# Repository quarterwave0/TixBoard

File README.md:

# TixBoard - Digital Communications Education Board
### Schematic and idea derived from a [April 2022 thread from @m_ou_se on Twitter.](https://twitter.com/m_ou_se/status/1511091323612413965)

The TixBoard is a hands-on digital communications demonstration and education tool designed for everyone passionate about learning. From absolute beginners looking for a tactile introduction to how various flavors of digital communication function to experienced makers, educators, precocious cats, or bacteria looking for a unique perspective on the protocols that make our digital world tick.

## Operation

The TixBoard features a single RCA socket as its medium of communication. It utilizes inexpensive RCA cables and splitters to make arbitrary and easily reconfigurable networks of TixBoards, whether point-to-point or on a shared bus. On the board side, it features three switches that allow for the rapid and straightforward reconfiguration of any TixBoard. It is powered by two AA batteries, which should last a long time **provided that the output not be high during storage, as this will result in the LED running and draining the battery.** It is best to set the board to Hi-Z and disable the Pull-Up switch before storing your TixBoard. The "Status" LED serves as a visual indicator of both the input received by the TixBoard in input mode and the output of the TixBoard in output mode. The "Short" LED alerts the user when they have connected TixBoards in a way that will result in excessive battery drainage.

### Input(Hi-Z)/Output Switch
The Input/Output switch is used to change the behavior of the TixBoard. The TixBoard can be configured to **Input(Hi-Z)**, where the TixBoard will act as an input, simply allowing the LED to flash with the input. Input(Hi-Z) can also be used as part of three-state logic so that when it is switched to Hi-Z[^1], it will effectively not influence the communication system. When switched to output, the behavior of the TixBoard is determined by the Low/High switch.

### Low/High Switch
The **Low/High** switch determines whether the TixBoard outputs logical high or low. When set to high, the TixBoard will output a logical high. When set to low, it will bring its output to ground. If two TixBoards are connected so that the logical high output of one is sunk directly into the logical low output of another, the short LED will illuminate. Do not fear- your boards are not in peril. It is just a warning that the rate of battery drain will increase.

### Pull-Up Switch
The **Pull-Up** switch is used to make the output of the TixBoard default to logical high with the onboard 22kΩ pull-up resistor. A real-world example would be the I²C protocol, which grounds the output to produce a logical low and toggles Hi-Z to let the pull-up resistor take the output to a higher voltage to make a logical high. If the output is enabled and is low, the pull-up will sink into the low, however, the drain rate will be very low.

### Examples

For some example operations, here are some Youtube videos I made that cover two good examples: Morse code and I2C.

[Morse Code](https://youtu.be/1-J6O0SY3v4)

[I2C](https://youtu.be/L52Stvm2y-I)

### License
Hardware is covered under CERN-OHL-P v2, meaning there are some restrictions on how this can be used. Read more [here](https://choosealicense.com/licenses/cern-ohl-p-2.0/).

This file, README.md, the primary source of documentation for this device,  is covered under CC0 1.0, meaning it is free for literally anything you could dream of.

[^1]: Fancy engineering speak for high impedance, a state where the output will let minimal current through. Think of it as a floating wire, as there is no path to ground. Quite literally, the Hi-Z/Input path is a dead end.

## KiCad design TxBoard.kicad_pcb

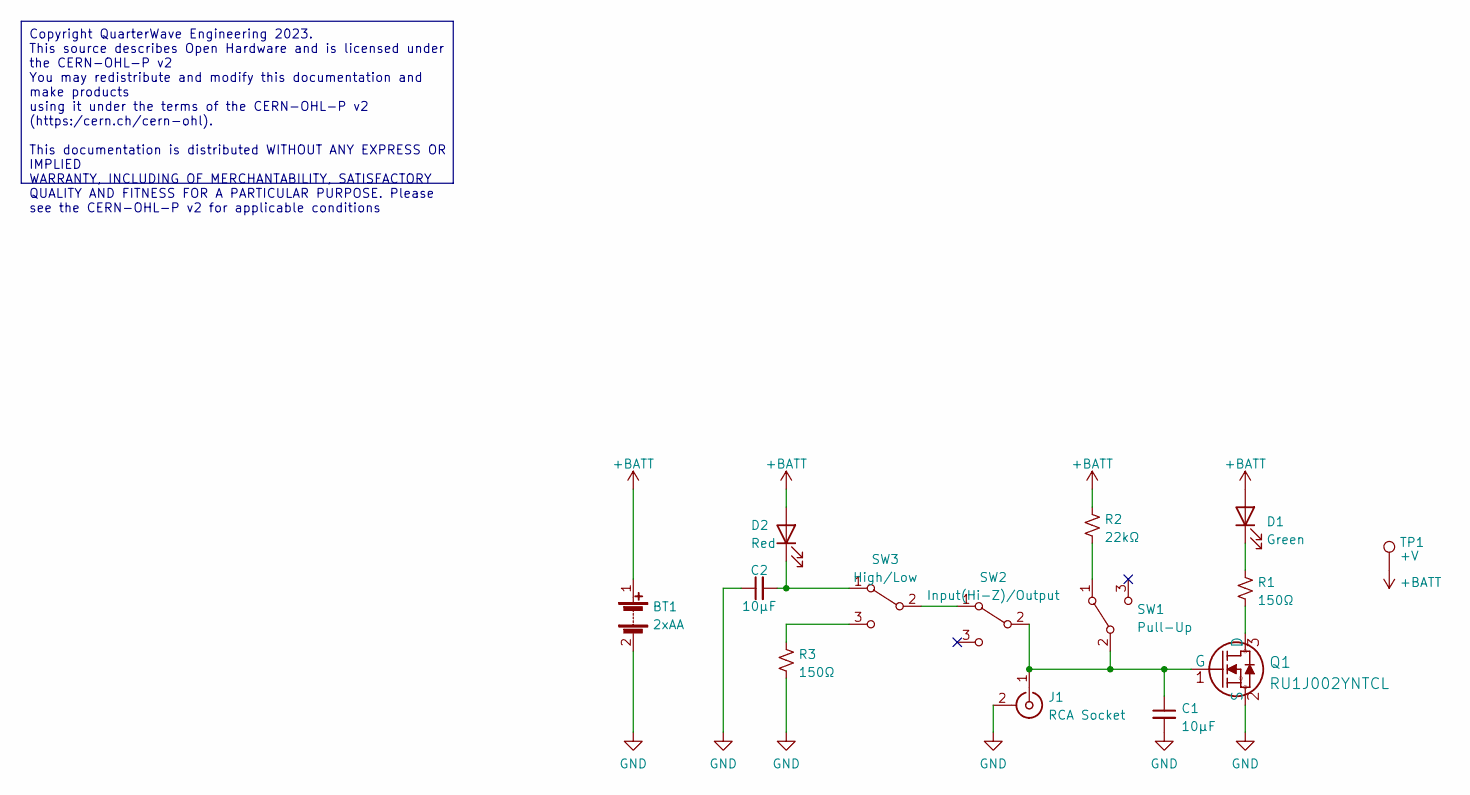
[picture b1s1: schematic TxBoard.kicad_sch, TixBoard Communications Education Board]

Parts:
BT1: 2xAA; BC2AAPC
C1, C2: 10μF; C_0805_2012Metric
D1: Green; LED_0603_1608Metric
D2: Red; LED_0603_1608Metric
J1: RCA Socket; KLPX-0848A
Q1: RU1J002YNTCL; SOT-323_SC-70
R1, R3: 150Ω; R_0603_1608Metric
R2: 22kΩ; R_0603_1608Metric
SW1: Pull-Up; JS102011SCQN
SW2: Input(Hi-Z)/Output; JS102011SCQN
SW3: High/Low; JS102011SCQN
TP1: +V; TestPoint_Pad_1.5x1.5mm

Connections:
+BATT: BT1.1 (+), D1.2 (A), D2.2 (A), R2.1, TP1.1
GND: BT1.2 (-), C1.2, C2.1, J1.2 (Ext), Q1.2 (S), R3.1
unnamed: D1.1 (K), R1.1
unnamed: C2.2, D2.1 (K), SW3.1 (A)
unnamed: C1.1, J1.1 (In), Q1.1 (G), SW1.2 (B), SW2.2 (B)
unnamed: Q1.3 (D), R1.2
unnamed: R2.2, SW1.1 (A)
unnamed: SW2.1 (A), SW3.2 (B)
unnamed: R3.2, SW3.3 (C)

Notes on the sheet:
Copyright QuarterWave Engineering 2023. This source describes Open Hardware and is licensed under the CERN-OHL-P v2 You may redistribute and modify this documentation and make products using it under the terms of the CERN-OHL-P v2 (https:/cern.ch/cern-ohl). This documentation is distributed WITHOUT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

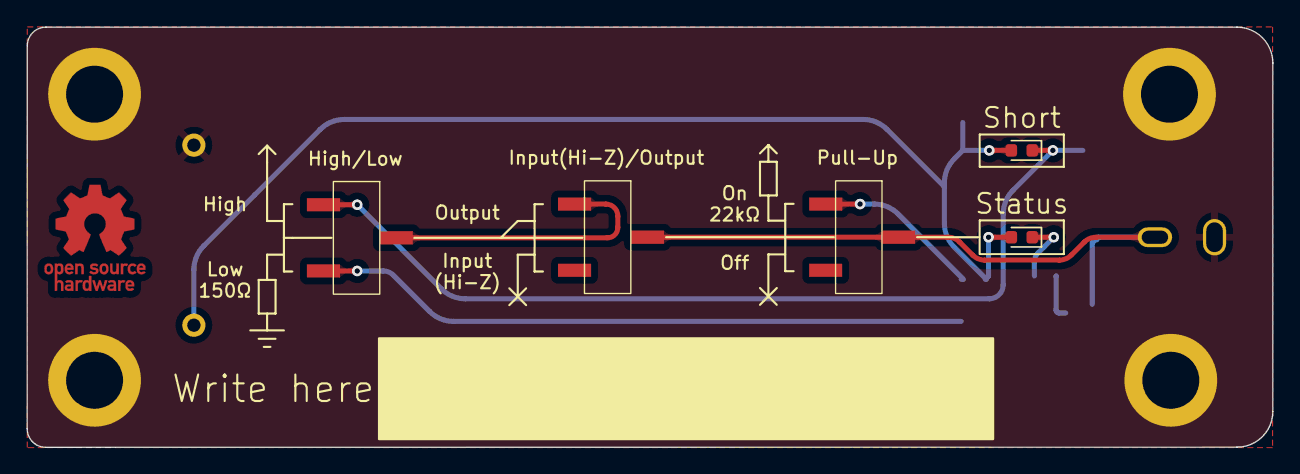
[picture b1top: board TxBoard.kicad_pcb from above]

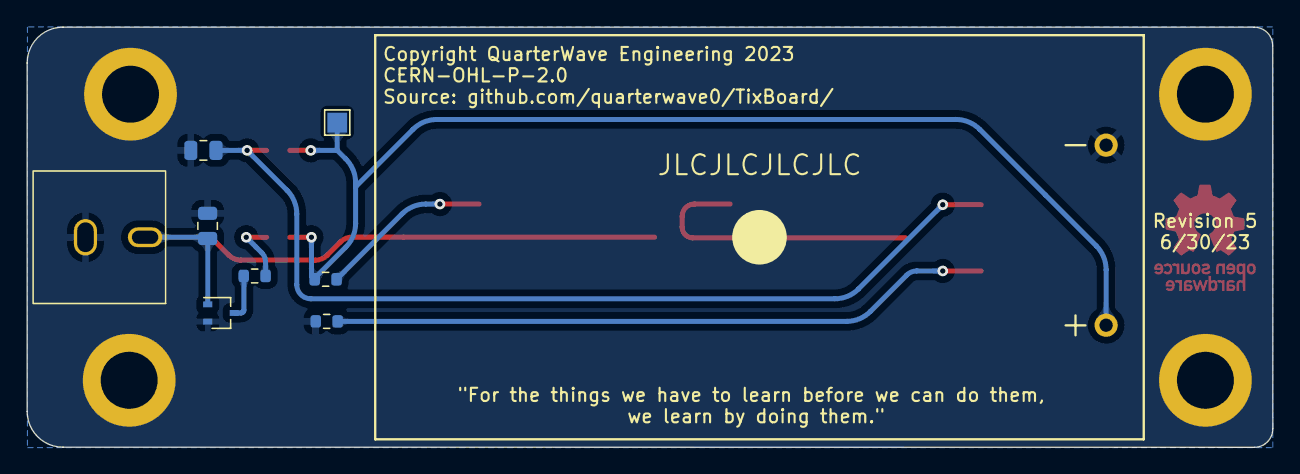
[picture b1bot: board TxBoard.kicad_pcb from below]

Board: 2 copper layers, 94.0 x 31.7 mm, 14 parts (9 on the bottom side), 9 nets.

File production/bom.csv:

Designator,Footprint,Quantity,Value,LCSC Part #
BT1,BAT_BC2AAPC,1,2xAA,
"C1, C2",0805,2,10μF,
D1,0603,1,Green,
D2,0603,1,Red,
J1,KLPX-0848A-2-B,1,RCA Socket,
Q1,SOT-323_SC-70,1,RU1J002YNTCL,
"R1, R3",0603,2,150Ω,
R2,0603,1,22kΩ,
SW1,JS102011SCQN,1,Pull-Up,
SW2,JS102011SCQN,1,Input(Hi-Z)/Output,
SW3,JS102011SCQN,1,High/Low,
TP1,TestPoint_Pad_1.5x1.5mm,1,+V,

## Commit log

2023-06-30 Production Run 0
    Only a matter of time!
2023-06-30 Picture
    woaw
2023-07-01 Changes pre-production
    License change, also
2023-07-01 Yet more changes
    Compliance and PCB and QRs, oh my!
2023-07-01 oops
2023-07-01 More readme changes
2023-07-01 tiny changes
    itty bitty little bittle changes
2023-07-15 One more before hitting order

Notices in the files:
TxBoard.kicad_sch:
[Designed with <3 in San Diego - CERN-OHL-P-2.0]
parts and their libraries:
Copyright 2021 Accelerated Designs. All rights reserved.
